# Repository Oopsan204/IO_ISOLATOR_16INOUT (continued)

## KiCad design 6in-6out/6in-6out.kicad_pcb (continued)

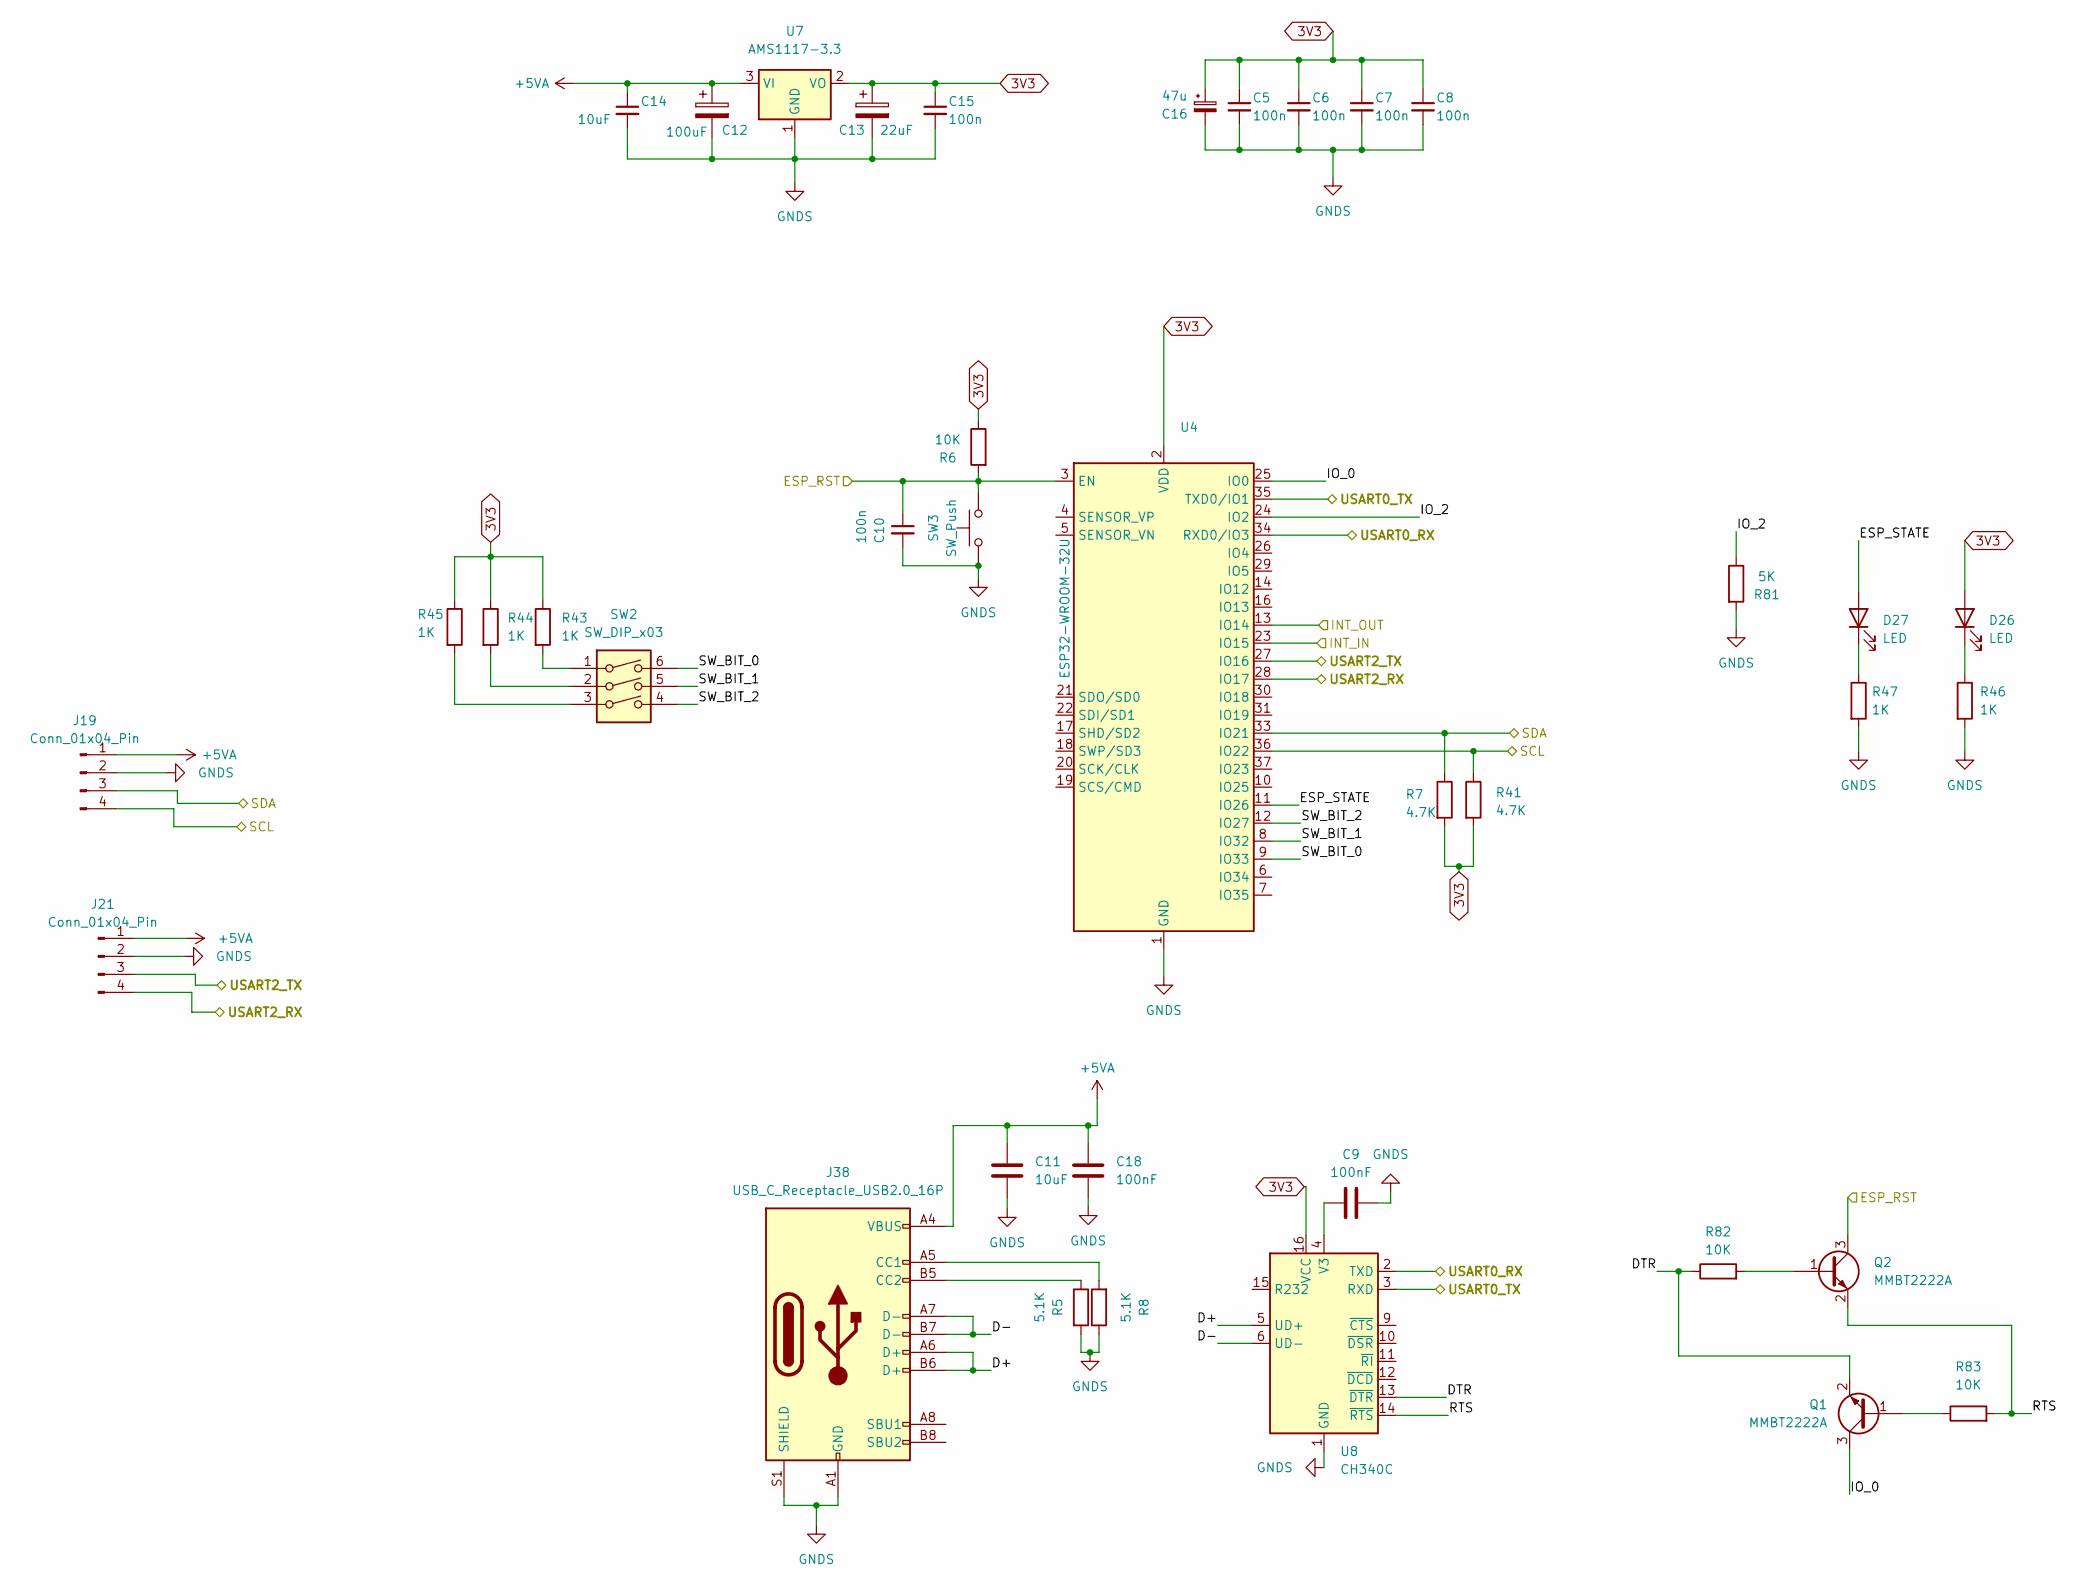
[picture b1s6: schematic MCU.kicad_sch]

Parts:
C5, C6, C7, C8, C10, C15: 100n; C_0603_1608Metric_Pad1.08x0.95mm_HandSolder; LCSC C482351
C9: 100nF; C_0603_1608Metric_Pad1.08x0.95mm_HandSolder
C11: 10uF; C_0603_1608Metric
C12: 100uF; C_0603_1608Metric_Pad1.08x0.95mm_HandSolder
C13: 22uF; C_0603_1608Metric_Pad1.08x0.95mm_HandSolder
C14: 10uF; C_0603_1608Metric_Pad1.08x0.95mm_HandSolder; LCSC C482351
C16: 47u; CP_EIA-3528-15_AVX-H; LCSC C185775
C18: 100nF; C_0603_1608Metric
D26, D27: LED; LED_0603_1608Metric_Pad1.05x0.95mm_HandSolder
J19, J21: Conn_01x04_Pin; JST 4
J38: USB_C_Receptacle_USB2.0_16P; USB_C_Receptacle_GCT_USB4105-xx-A_16P_TopMnt_Horizontal
Q1, Q2: MMBT2222A; SOT-23
R5, R8: 5.1K; C_0603_1608Metric
R6: 10K; R_0603_1608Metric_Pad0.98x0.95mm_HandSolder; LCSC C269701
R7, R41: 4.7K; R_0603_1608Metric_Pad0.98x0.95mm_HandSolder
R43, R44, R45, R46, R47: 1K; R_0805_2012Metric_Pad1.20x1.40mm_HandSolder
R81: 5K; R_0603_1608Metric_Pad0.98x0.95mm_HandSolder; LCSC C3202451
R82, R83: 10K; R_0603_1608Metric_Pad0.98x0.95mm_HandSolder
SW2: SW_DIP_x03
SW3: SW_Push; SW_Tactile_SPST_NO_Straight_CK_PTS636Sx25SMTRLFS; LCSC C7435503
U4: ESP32-WROOM-32U; LCSC C701346
U7: AMS1117-3.3; SOT-223-3_TabPin2
U8: CH340C; SOIC-16_3.9x9.9mm_P1.27mm

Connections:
3V3: C5.1, C6.1, C7.1, C8.1, C13.1, C15.1, C16.1, D26.2 (A), R6.1, R7.2, R41.2, R43.1, R44.1, R45.1, U4.2 (VDD), U7.2 (VO), U8.16 (VCC); also elsewhere on the board
+5VA: C11.1, C12.1, C14.1, C18.1, J19.1, J21.1, J38.A4 (VBUS), J38.A9 (VBUS), J38.B4 (VBUS), J38.B9 (VBUS), U7.3 (VI); also elsewhere on the board
/MCU/D+: J38.A6 (D+), J38.B6 (D+), U8.5 (UD+)
/MCU/D-: J38.A7 (D-), J38.B7 (D-), U8.6 (UD-)
/MCU/DTR: Q1.2 (E), R82.1, U8.13 (~DTR)
/MCU/ESP_RST: C10.1, Q2.3 (C), R6.2, SW3.2, U4.3 (EN)
/MCU/ESP_STATE: D27.2 (A), U4.11 (IO26)
/MCU/INT_IN: U4.23 (IO15); also elsewhere on the board
/MCU/INT_OUT: U4.13 (IO14); also elsewhere on the board
/MCU/IO_0: Q1.3 (C), U4.25 (IO0)
/MCU/IO_2: R81.1, U4.24 (IO2)
/MCU/RTS: Q2.2 (E), R83.2, U8.14 (~RTS)
/MCU/SCL: J19.4, R41.1, U4.36 (IO22); also elsewhere on the board
/MCU/SDA: J19.3, R7.1, U4.33 (IO21); also elsewhere on the board
/MCU/SW_BIT_0: SW2.6, U4.9 (IO33)
/MCU/SW_BIT_1: SW2.5, U4.8 (IO32)
/MCU/SW_BIT_2: SW2.4, U4.12 (IO27)
/MCU/USART0_RX: U4.34 (RXD0/IO3), U8.2 (TXD)
/MCU/USART0_TX: U4.35 (TXD0/IO1), U8.3 (RXD)
/MCU/USART2_RX: J21.4, U4.28 (IO17)
/MCU/USART2_TX: J21.3, U4.27 (IO16)
GNDS: C5.2, C6.2, C7.2, C8.2, C9.1, C10.2, C11.2, C12.2, C13.2, C14.2, C15.2, C16.2, C18.2, J19.2, J21.2, J38.A1 (GND), J38.A12 (GND), J38.B1 (GND), J38.B12 (GND), J38.S1 (SHIELD), R5.2, R8.1, R46.2, R47.2, R81.2, SW3.1, U4.1 (GND), U4.15 (GND), U4.38 (GND), U4.39 (GND), U7.1 (GND), U8.1 (GND); also elsewhere on the board
unnamed: D26.1 (K), R46.1
unnamed: D27.1 (K), R47.1
unnamed: J38.A5 (CC1), R8.2
unnamed: J38.B5 (CC2), R5.1
unnamed: Q1.1 (B), R83.1
unnamed: Q2.1 (B), R82.2
unnamed: R43.2, SW2.1
unnamed: R44.2, SW2.2
unnamed: R45.2, SW2.3
unnamed: C9.2, U8.4 (V3)

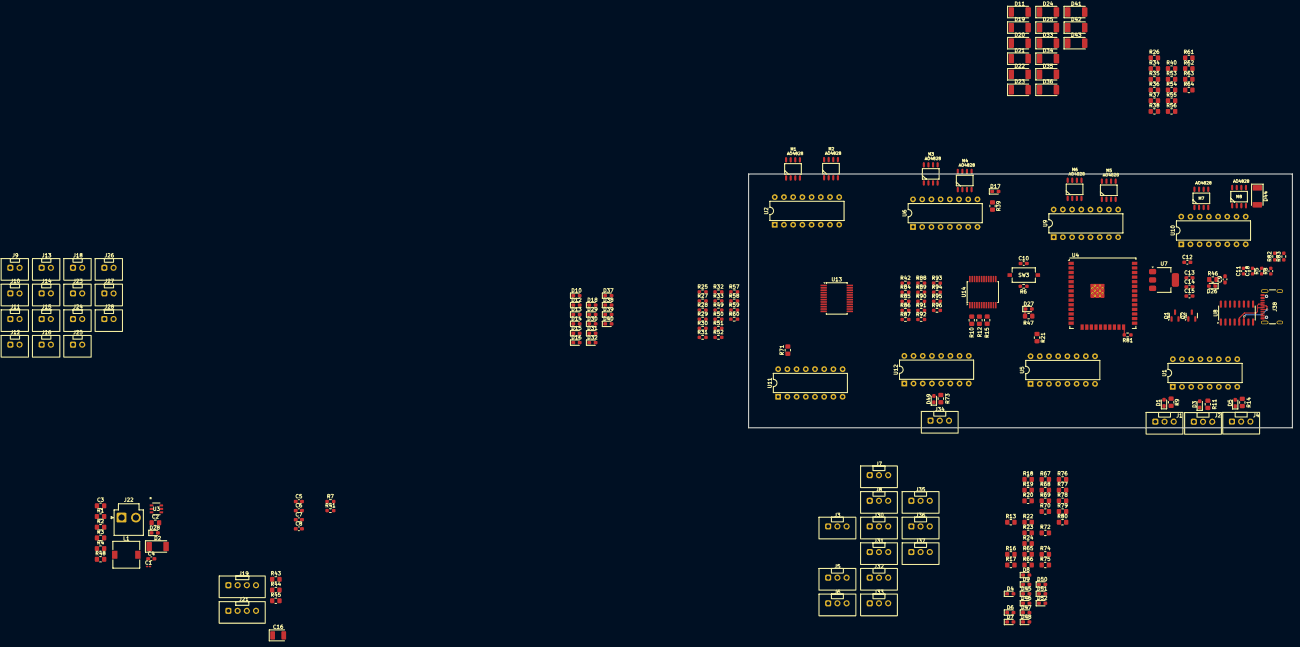
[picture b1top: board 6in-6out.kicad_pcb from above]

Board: 2 copper layers, 150.0 x 70.0 mm, 226 parts (0 on the bottom side), 183 nets.

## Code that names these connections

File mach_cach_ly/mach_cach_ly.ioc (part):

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Mcu.Name=STM32F103C(8-B)Tx
Mcu.Package=LQFP48
Mcu.UserName=STM32F103C8Tx
PA10.Mode=Asynchronous
PA10.Signal=USART1_RX
PA11.Mode=CAN_Activate
PA11.Signal=CAN_RX
PA12.Mode=CAN_Activate
PA12.Signal=CAN_TX
PA13.Mode=Serial_Wire
PA13.Signal=SYS_JTMS-SWDIO
PA14.Mode=Serial_Wire
PA14.Signal=SYS_JTCK-SWCLK
PA2.Mode=Asynchronous
PA2.Signal=USART2_TX
PA3.Mode=Asynchronous
PA3.Signal=USART2_RX
PA4.GPIOParameters=GPIO_Label
PA4.GPIO_Label=OUTPUT_0
PA4.Signal=GPIO_Output
PA5.GPIOParameters=GPIO_Label
PA5.GPIO_Label=OUTPUT_1
PA5.Signal=GPIO_Output
PA6.GPIOParameters=GPIO_Label
PA6.GPIO_Label=OUTPUT_2
PA6.Signal=GPIO_Output
PA7.GPIOParameters=GPIO_Label
PA7.GPIO_Label=OUTPUT_3
PA7.Signal=GPIO_Output
PA8.GPIOParameters=GPIO_Label
PA8.GPIO_Label=INPUT_0
PA8.Signal=GPIO_Input
PA9.Mode=Asynchronous
PA9.Signal=USART1_TX
PB0.GPIOParameters=GPIO_Label
PB0.GPIO_Label=OUTPUT_4
PB0.Signal=GPIO_Output
PB1.GPIOParameters=GPIO_Label
PB1.GPIO_Label=OUTPUT_5
PB1.Signal=GPIO_Output
PB10.GPIOParameters=GPIO_Label
PB10.GPIO_Label=OUTPUT_7
PB10.Signal=GPIO_Output
PB12.GPIOParameters=GPIO_Label
PB12.GPIO_Label=INPUT_4
PB12.Signal=GPIO_Input
PB13.GPIOParameters=GPIO_Label
PB13.GPIO_Label=INPUT_3
PB13.Signal=GPIO_Input
PB14.GPIOParameters=GPIO_Label
PB14.GPIO_Label=INPUT_2
PB14.Signal=GPIO_Input
PB15.GPIOParameters=GPIO_Label
PB15.GPIO_Label=INPUT_1
PB15.Signal=GPIO_Input
PB2.GPIOParameters=GPIO_Label
PB2.GPIO_Label=OUTPUT_6
PB2.Signal=GPIO_Output
PB3.GPIOParameters=GPIO_Label
PB3.GPIO_Label=INPUT_7
PB3.Signal=GPIO_Input
PB4.GPIOParameters=GPIO_Label
PB4.GPIO_Label=INPUT_6
PB4.Signal=GPIO_Input
PB5.GPIOParameters=GPIO_Label
PB5.GPIO_Label=INPUT_5
PB5.Signal=GPIO_Input
PB6.Mode=I2C
PB6.Signal=I2C1_SCL
PB7.Mode=I2C
PB7.Signal=I2C1_SDA
PB8.GPIOParameters=GPIO_Label
PB8.GPIO_Label=LED
PB8.Signal=GPIO_Output
PC13-TAMPER-RTC.GPIOParameters=GPIO_Label
PC13-TAMPER-RTC.GPIO_Label=SW_BIT_0
PC13-TAMPER-RTC.Signal=GPIO_Input
PC14-OSC32_IN.GPIOParameters=GPIO_Label
PC14-OSC32_IN.GPIO_Label=SW_BIT_1
PC14-OSC32_IN.Signal=GPIO_Input
PC15-OSC32_OUT.GPIOParameters=GPIO_Label
PC15-OSC32_OUT.GPIO_Label=SW_BIT_2
PC15-OSC32_OUT.Signal=GPIO_Input
RCC.HSEDivPLL=RCC_HSE_PREDIV_DIV2
RCC.HSE_VALUE=16000000
RCC.SYSCLKFreq_VALUE=8000000
RCC.SYSCLKSource=RCC_SYSCLKSOURCE_PLLCLK
board=custom

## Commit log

2025-04-19 Initial commit.
2025-04-19 Test Commit.
2025-06-11 no message
